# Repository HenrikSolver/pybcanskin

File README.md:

pybcanskin
==========

Basic skin for pyboard with two CAN bus transceivers.
The BOM says that the CAN tranceiver TJA1051T/3 is used.
In the real world I use TJF1051/3, they are pin compatible.

Note that the power the tranceiver comes from Vin in 
the pyboard. This means that you should not supply more than 
5V to the board. Using power from USB works fine. 

Link to PCB at OSH park
<a href="https://oshpark.com/shared_projects/ZzbDCTR0"></img></a>

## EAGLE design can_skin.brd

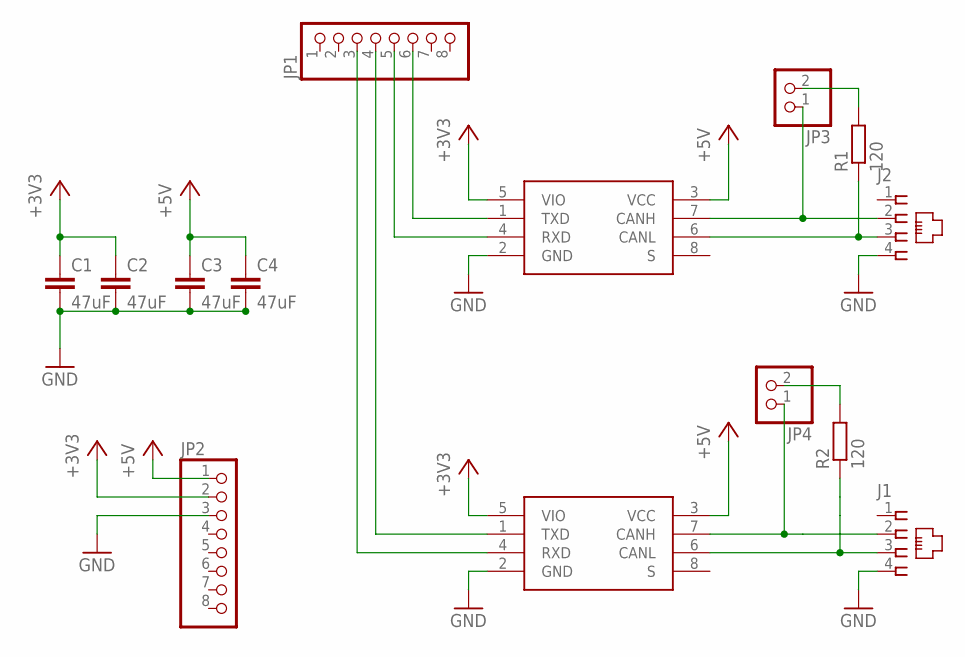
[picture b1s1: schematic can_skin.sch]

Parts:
C1, C2, C3, C4: 47uF; C3216
J1, J2: 215875-3
JP1, JP2: PINHD-1X8; 1X08
JP3, JP4: PINHD-1X2; 1X02
R1, R2: 120; M3216
U1, U2: TJA1051T/3; SOIC127P600X175-8N

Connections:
+3V3: C1.1, C2.1, JP2.2, U1.5 (VIO), U2.5 (VIO)
+5V: C3.1, C4.1, JP2.1, U1.3 (VCC), U2.3 (VCC)
GND: C1.2, C2.2, C3.2, C4.2, J1.4, J2.4, JP2.3, U1.2 (GND), U2.2 (GND)
unnamed: J1.2, JP4.1, U1.7 (CANH)
unnamed: J1.3, R2.1, U1.6 (CANL)
unnamed: JP1.5, U2.4 (RXD)
unnamed: J2.3, R1.1, U2.6 (CANL)
unnamed: J2.2, JP3.1, U2.7 (CANH)
unnamed: JP4.2, R2.2
unnamed: JP3.2, R1.2
unnamed: JP1.6, U2.1 (TXD)
unnamed: JP1.3, U1.4 (RXD)
unnamed: JP1.4, U1.1 (TXD)

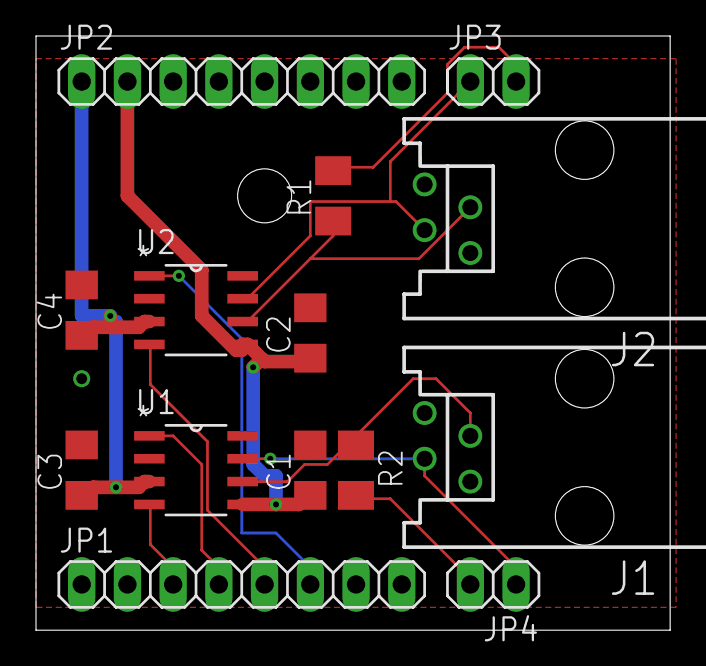
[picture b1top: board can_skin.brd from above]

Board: 2 copper layers, 35.2 x 33.0 mm, 14 parts (0 on the bottom side), 13 nets.

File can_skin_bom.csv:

"Part";"Value";"Device";"Package";"Description";"MPN";"OC_FARNELL";"OC_NEWARK";"PACKAGE";"SPICEPREFIX";"SUPPLIER";
"C1";"47uF";"C-EUC3216";"C3216";"CAPACITOR, European symbol";"";"";"";"";"C";"";
"C2";"47uF";"C-EUC3216";"C3216";"CAPACITOR, European symbol";"";"";"";"";"C";"";
"C3";"47uF";"C-EUC3216";"C3216";"CAPACITOR, European symbol";"";"";"";"";"C";"";
"C4";"47uF";"C-EUC3216";"C3216";"CAPACITOR, European symbol";"";"";"";"";"C";"";
"J1";"";"215875-3";"215875-3";"AMP connector";"";"";"";"";"";"";
"J2";"";"215875-3";"215875-3";"AMP connector";"";"";"";"";"";"";
"JP1";"";"PINHD-1X8";"1X08";"PIN HEADER";"";"";"";"";"";"";
"JP2";"";"PINHD-1X8";"1X08";"PIN HEADER";"";"";"";"";"";"";
"JP3";"";"PINHD-1X2";"1X02";"PIN HEADER";"";"";"";"";"";"";
"JP4";"";"PINHD-1X2";"1X02";"PIN HEADER";"";"";"";"";"";"";
"R1";"120";"R-EU_M3216";"M3216";"RESISTOR, European symbol";"";"";"";"";"R";"";
"R2";"120";"R-EU_M3216";"M3216";"RESISTOR, European symbol";"";"";"";"";"R";"";
"U1";"TJA1051T/3";"TJA1051T/3";"SOIC127P600X175-8N";"High speed CAN transceiver";"TJA1051T/3";"-";"99R3114";"SOIC-8";"";"NXP Semiconductor";
"U2";"TJA1051T/3";"TJA1051T/3";"SOIC127P600X175-8N";"High speed CAN transceiver";"TJA1051T/3";"-";"99R3114";"SOIC-8";"";"NXP Semiconductor";

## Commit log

2014-12-18 Adding project files.
2014-12-18 Updated README file.
2014-12-18 Add a picture
2017-02-28 Added link to OSHpark
2017-02-28 Added a pdf of schematic
